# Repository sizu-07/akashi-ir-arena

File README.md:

# 明石光線

4人が1対1対1対1で遊ぶ赤外線対戦システムです。銃側はXIAO ESP32-S3 Plus、赤外線受信機3個、赤外線送信、テープLED、振動モーター、トリガー1個を使用し、Windows PCが試合を管理します。銃にブザーやリロードボタンはありません。運営はiPad、観客表示とカウントダウン音声・BGMはPCに接続したプロジェクターから操作します。現行ルールは実時間85秒・画面表示90秒×3ゲーム・1発撃破・7秒自動復活・合計キル数勝負です。詳細は [ゲーム仕様 v0.8](docs/ゲーム仕様_v0.8.md) を参照してください。

射撃・被弾・撃破・復活・試合終了の効果音は、[音声ファイルの配置方法](assets/audio/README.md)に従い `assets/audio/effects/` に入れると投影画面から再生できます。

## 現在の状態

- PC管理プログラム、iPad運営画面、投影画面、ESP32ファームウェアを収録しています。
- 来場者向け整理券受付・待機表示、整理券運営、入場QR読取、ゲーム状態連携を収録しています。
- 回路設計と銃の3Dモデルは別担当です。`hardware/circuit/` の既存KiCadデータは旧構成で、現行ゲーム版との実機確認は未完了です。
- 電気・機械設計に必要な接続条件は `specs/` にあります。
- player1〜4の個人戦用BINは `firmware/release/players-4e/` に生成済みです。4台同時の試合、連続稼働、会場での確認は未実施です。旧v0.7以前のBINは個人戦に使用できません。

## 実行方法

1. Node.js 20以上をインストールします。
2. 動作確認は `起動_デモ.cmd`、実機4台での本番運営は `起動_本番.cmd` を開きます。
3. 初回だけ必要なパッケージと設定が準備され、ゲーム運営画面が自動的に開きます。
4. ゲーム運営画面は `http://localhost:8080/`、投影画面は `http://localhost:8080/display` です。
5. 整理券の運営・来場者受付・入場QR読取は、ゲーム運営画面上部から公開サーバーの各画面を開きます。

タブレットの運営画面は、PCと同じWi-Fiに接続し、PCのWi-Fi側IPv4アドレスを使って `http://<PCのWi-Fiアドレス>:8080/` を開きます。PCの `localhost` や基板用Ethernetの `192.168.137.1` はタブレットからの接続先ではありません。PCの投影画面にある「タブレット接続QR」もWi-Fi側アドレスを表示します。IPアドレスはネットワーク接続時に変わる場合があります。

`起動_デモ.cmd` と `起動_本番.cmd` を切り替えるときは、同じポートで動いているこのシステムの旧サーバーを自動終了してから、選んだモードで起動し直します。別のアプリが8080番ポートを使っている場合は、安全のため自動終了しません。

デモ版では「デモの確認対象」で「仮想端末4台（実機なし）」と「接続した実機」を切り替えます。実機を選ぶと仮想端末を停止し、「接続済み端末だけで動作確認」で1台から開始できます。投影画面の「表示を準備」と、参加端末の接続・時刻同期・構成確認が必要です。待機中、動作確認の途中経過表示中、または終了後に切り替えられ、切り替えると戦績・残り時間を戻します。確認対象は次回のデモ起動にも引き継ぎます。実機のWi-Fi設定・端末キーは本番と共通です。デモ版は公開整理券サーバーへゲーム連携通信を行いません。

本番版には動作確認・実機モーターデモの操作を表示しません。通常ゲーム用の4台、電池状態、投影準備、開始ACKを確認して通常試合を開始します。整理券連携が設定済みなら、先に「整理券メンバーを反映」を実行してください。本番APIからの動作確認要求も拒否します。

本番では第1〜2ゲームの終了後に途中経過を15秒表示し、4台と投影画面の準備が整えば次のカウントダウンへ自動で進みます。デモでは「このゲームを終了して途中経過へ」で時間を短縮し、次ゲームを手動開始できます。両モードの「試合全体を強制終了」は残りゲームを省略します。整理券は4名全員が入場確認されるまで通常試合へ進めません。処理の分担と運営手順は [ゲーム仕様 v0.8](docs/ゲーム仕様_v0.8.md) にまとめています。

`npm run validate` はソフトウェア・4台分のBIN・実機試験記録を別々に確認します。4台同時の実機試験は未実施なので、[実機試験記録](tests/実機試験記録.csv) の v0.8 項目が完了するまで総合判定は不合格になります。

整理券の正本は公開サーバーとSupabaseに一元化しています。ローカルに別の整理券サーバーを起動しないでください。詳細は [整理券システム 運用・配置手順](docs/整理券システム.md) を参照。

~~詳しい手順は次の順で読んでください。~~

~~1. [概要と仕様](docs/01_概要と仕様.md)
2. [製作・Wi-Fi・書込み](docs/02_製作手順.md)
3. [運営と投影の操作](docs/03_操作手順.md)
4. [実機の完成確認](docs/04_完成確認チェック.md)
5. [開発者向け案内](docs/05_開発者向け.md)~~
未定のため修正中。決まり次第記入予定。

## フォルダ構成

| 場所 | 内容 |
|---|---|
| `apps/server/` | Windows PCで動く試合管理・通信サーバー |
| `apps/web/` | iPad運営画面とプロジェクター投影画面 |
| `apps/ticket-server/` | 外部整理券API、割当、認証、履歴、WebSocket |
| `apps/ticket-web/` | 来場者受付・整理券・運営・入場QR読取画面 |
| `assets/` | ルール説明動画などの共通素材 |
| `firmware/` | XIAO ESP32-S3 Plus用プログラムと書込み用BIN |
| `specs/` | GPIO、受信機3個、モーターなどのハードウェア要求 |
| `hardware/circuit/` | 回路担当者の提出先（既存KiCadデータは旧構成） |
| `hardware/gun-model/` | 銃モデル担当者の提出先 |
| `docs/` | 仕様、製作、操作、試験の説明書 |
| `tools/` | セットアップ、ビルド、書込み、検証用ツール |
| `tests/` | 自動テストと実機試験記録 |

`config/`、`data/`、`logs/`、`.local-archive/` は各PCだけで使い、GitHubには共有しません。Wi-Fiパスワード、運営PIN、銃ごとの鍵も共有しないでください。

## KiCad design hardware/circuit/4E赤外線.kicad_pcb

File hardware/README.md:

# ハードウェア担当者用

回路設計と銃の3Dモデルは別担当者が作成します。`circuit/` に残るKiCadデータは旧構成です。

- 回路・PCBデータの提出先：`circuit/`
- 銃の3Dモデル・STL・組立図の提出先：`gun-model/`
- 共通の要求条件：`../specs/hardware-profile.json`
- 部品候補と変更点：`../specs/component-plan.csv`
- ゲーム・操作・表示条件：`../docs/ゲーム仕様_v0.7.md`
- 検査条件：`../tests/実機試験記録.csv`

現在の `circuit/` のKiCadデータは旧構成を含み、v0.7の実装確認済み回路ではありません。新設計では銃の操作入力をトリガー1個にし、リロード・モード用スイッチとブザーを設けず、6個のLEDと振動モーターを接続してください。銃IDとWi-FiはUSBで登録するため、組立後もUSB端子にアクセスできる筐体が必要です。電源の投入・遮断方法は回路・筐体担当者が確定してください。

担当者は採用部品、端子割当、電源定格、基板寸法、取付位置が確定した時点で、このREADMEも更新してください。特に射撃時の短い振動と赤外線送信が同時に動作する際の電圧降下を実測してください。

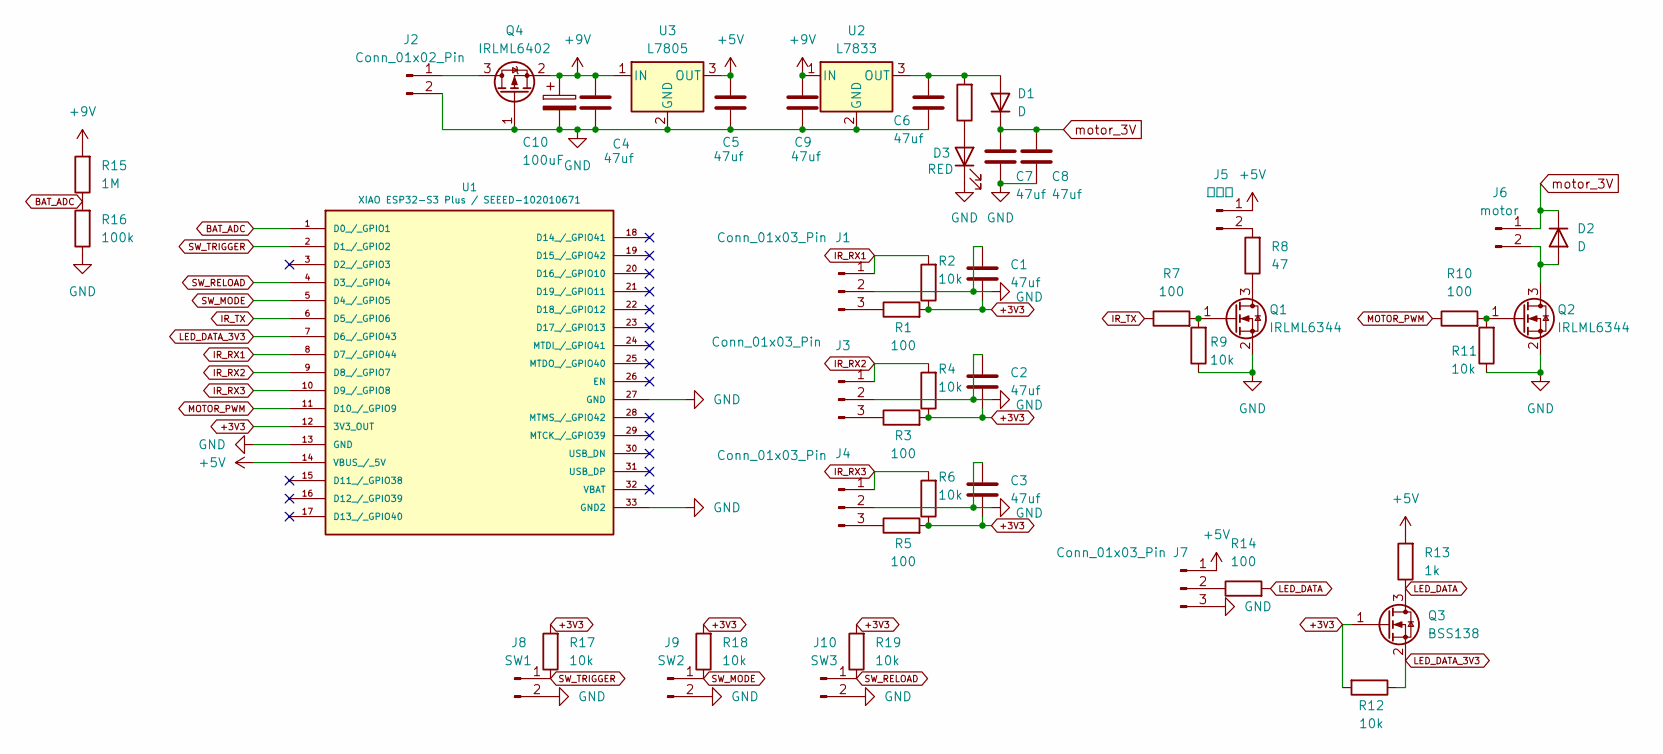
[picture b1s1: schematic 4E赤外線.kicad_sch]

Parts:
C1, C2, C3, C4, C5, C6, C9: 47uf; C_0603_1608Metric
C7, C8: 47uf; C_0805_2012Metric
C10: 100uF; CP_Elec_8x6.5
D1, D2: D; D_MicroSMP_AK
D3: RED; LED_0603_1608Metric
J1, J3, J4, J7: Conn_01x03_Pin; JST_XH_B3B-XH-A_1x03_P2.50mm_Vertical
J2: Conn_01x02_Pin; JST_XH_B2B-XH-A_1x02_P2.50mm_Vertical
J5: 赤外線; JST_XH_B2B-XH-A_1x02_P2.50mm_Vertical
J6: motor; JST_XH_B2B-XH-A_1x02_P2.50mm_Vertical
J8: SW1; JST_XH_B2B-XH-A_1x02_P2.50mm_Vertical
J9: SW2; JST_XH_B2B-XH-A_1x02_P2.50mm_Vertical
J10: SW3; JST_XH_B2B-XH-A_1x02_P2.50mm_Vertical
Q1, Q2: IRLML6344; SOT-23
Q3: BSS138; SOT-23
Q4: IRLML6402; SOT-23
R1, R3, R5, R7, R10, R14: 100; R_0603_1608Metric
R2, R4, R6, R9, R11, R12, R17, R18, R19: 10k; R_0603_1608Metric
R8: 47; R_0603_1608Metric
R13: 1k; R_0603_1608Metric
R15: 1M; R_0805_2012Metric
R16: 100k; R_0805_2012Metric
R20: 1k; R_0603_1608Metric; LCSC C23345
U1: XIAO ESP32-S3 Plus / SEEED-102010671; XIAO-ESP32-S3-Plus-SMD; MPN SEEED-102010671
U2: L7833; TO-252-3-L1_NMD
U3: L7805; TO-252-3-L1_NMD

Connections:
+3V3: C1.2, C2.2, C3.2, Q3.1 (G), R1.2, R2.1, R3.2, R4.1, R5.2, R6.1, R12.2, R17.2, R18.2, R19.2, U1.12 (3V3_OUT)
+5V: C5.1, J5.1, J7.1, R13.2, U1.14 (VBUS_/_5V), U3.3 (OUT)
+9V: C4.1, C9.1, C10.1, Q4.2 (S), R15.2, U2.1 (IN), U3.1 (IN)
BAT_ADC: R15.1, R16.2, U1.1 (D0_/_GPIO1)
GND: C1.1, C2.1, C3.1, C4.2, C5.2, C6.2, C7.2, C8.2, C9.2, C10.2, D3.1 (K), J1.2, J2.2, J3.2, J4.2, J7.3, J8.2, J9.2, J10.2, Q1.2 (S), Q2.2 (S), Q4.1 (G), R9.1, R11.1, R16.1, U1.13 (GND), U1.27 (GND), U1.33 (GND2), U2.2 (GND), U3.2 (GND)
IR_RX1: J1.1, R2.2, U1.8 (D7_/_GPIO44)
IR_RX2: J3.1, R4.2, U1.9 (D8_/_GPIO7)
IR_RX3: J4.1, R6.2, U1.10 (D9_/_GPIO8)
IR_TX: R7.1, U1.6 (D5_/_GPIO6)
LED_DATA: Q3.3 (D), R13.1, R14.2
LED_DATA_3V3: Q3.2 (S), R12.1, U1.7 (D6_/_GPIO43)
MOTOR_PWM: R10.1, U1.11 (D10_/_GPIO9)
unnamed: C6.1, D1.2 (A), R20.2, U2.3 (OUT)
unnamed: D2.2 (A), J6.2, Q2.3 (D)
unnamed: D3.2 (A), R20.1
unnamed: J1.3, R1.1
unnamed: J2.1, Q4.3 (D)
unnamed: J3.3, R3.1
unnamed: J4.3, R5.1
unnamed: J5.2, R8.2
unnamed: J7.2, R14.1
unnamed: Q1.3 (D), R8.1
unnamed: Q1.1 (G), R7.2, R9.2
unnamed: Q2.1 (G), R10.2, R11.2
SW_MODE: J9.1, R18.1, U1.5 (D4_/_GPIO5)
SW_RELOAD: J10.1, R19.1, U1.4 (D3_/_GPIO4)
SW_TRIGGER: J8.1, R17.1, U1.2 (D1_/_GPIO2)
motor_3V: C7.1, C8.1, D1.1 (K), D2.1 (K), J6.1

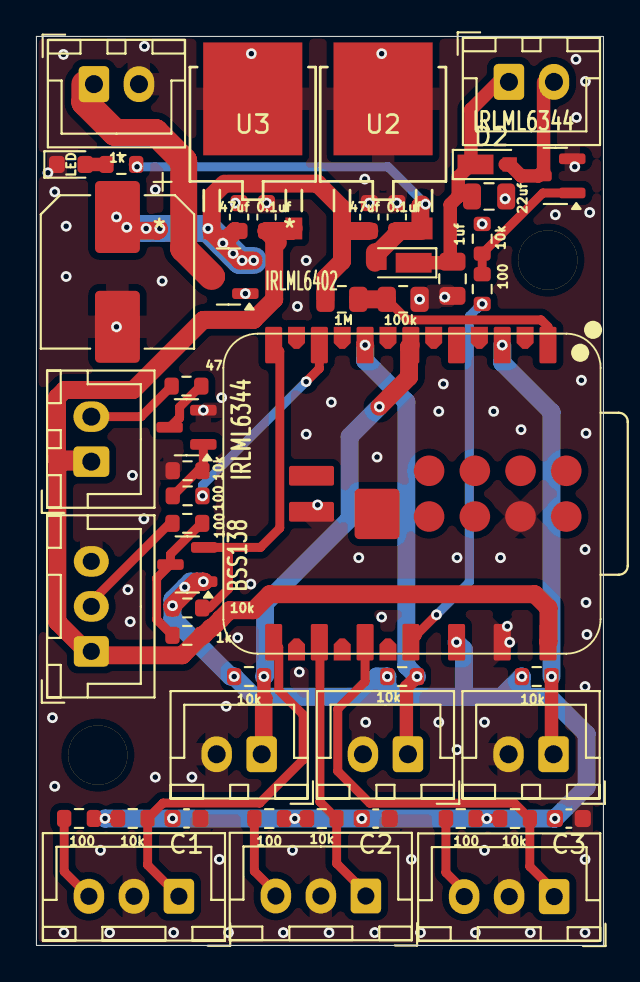
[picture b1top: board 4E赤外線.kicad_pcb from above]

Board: 2 copper layers, 31.5 x 50.5 mm, 50 parts (0 on the bottom side), 28 nets.

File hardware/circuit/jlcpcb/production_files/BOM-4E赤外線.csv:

Comment,Designator,Footprint,LCSC,Quantity
1k,R20,R_0603_1608Metric,C23345,1
47uf,"C1,C2,C3,C4,C5,C6,C9",C_0603_1608Metric,C140782,7
IRLML6344,Q1,SOT-23,,1
10k,R9,R_0603_1608Metric,,1
47,R8,R_0603_1608Metric,,1
100,R7,R_0603_1608Metric,,1
Conn_01x03_Pin,J7,JST_XH_B3B-XH-A_1x03_P2.50mm_Vertical,,1
10k,R11,R_0603_1608Metric,,1
D,D2,D_MicroSMP_AK,,1
C_Polarized,C10,CP_Elec_8x6.5,,1
47uf,C7,C_0805_2012Metric,,1
Conn_01x02_Pin,J2,JST_XH_B2B-XH-A_1x02_P2.50mm_Vertical,,1
IRLML6402,Q4,SOT-23,,1
LED,D3,LED_0603_1608Metric,,1
D,D1,D_MicroSMP_AK,,1
1M,R15,R_0805_2012Metric,,1
motor,J6,JST_XH_B2B-XH-A_1x02_P2.50mm_Vertical,,1
L7805,U3,TO-252-3-L1_NMD,,1
100k,R16,R_0805_2012Metric,,1
IRLML6344,Q2,SOT-23,,1
100,R10,R_0603_1608Metric,,1
47uf,C8,C_0805_2012Metric,,1
L7833,U2,TO-252-3-L1_NMD,,1
赤外線,J5,JST_XH_B2B-XH-A_1x02_P2.50mm_Vertical,,1
XIAO ESP32-S3 Plus / SEEED-102010671,U1,XIAO-ESP32-S3-Plus-SMD,,1
10k,R12,R_0603_1608Metric,,1
100,R3,R_0603_1608Metric,,1
Conn_01x03_Pin,J3,JST_XH_B3B-XH-A_1x03_P2.50mm_Vertical,,1
Conn_01x03_Pin,J4,JST_XH_B3B-XH-A_1x03_P2.50mm_Vertical,,1
10k,R4,R_0603_1608Metric,,1
Conn_01x03_Pin,J1,JST_XH_B3B-XH-A_1x03_P2.50mm_Vertical,,1
10k,R6,R_0603_1608Metric,,1
100,R14,R_0603_1608Metric,,1
BSS138,Q3,SOT-23,,1
SW2,J9,JST_XH_B2B-XH-A_1x02_P2.50mm_Vertical,,1
1k,R13,R_0603_1608Metric,,1
10k,R19,R_0603_1608Metric,,1
10k,R17,R_0603_1608Metric,,1
100,R5,R_0603_1608Metric,,1
SW3,J10,JST_XH_B2B-XH-A_1x02_P2.50mm_Vertical,,1
100,R1,R_0603_1608Metric,,1
SW1,J8,JST_XH_B2B-XH-A_1x02_P2.50mm_Vertical,,1
10k,R2,R_0603_1608Metric,,1
10k,R18,R_0603_1608Metric,,1

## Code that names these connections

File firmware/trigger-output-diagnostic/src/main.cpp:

#include <Arduino.h>
#include <driver/rmt.h>

#if !CONFIG_IDF_TARGET_ESP32S3
#error "Trigger output diagnostic requires XIAO ESP32-S3 Plus"
#endif

// Legacy 4E赤外線 PCB. These pins differ from the current v0.7 profile.
constexpr uint8_t SW1_PIN = 2;       // J8 / SW_TRIGGER, closed to GND
constexpr uint8_t SW2_PIN = 5;       // J9 / SW_MODE
constexpr uint8_t SW3_PIN = 4;       // J10 / SW_RELOAD
constexpr uint8_t MOTOR_PIN = 9;     // MOTOR_PWM -> Q2 gate
constexpr uint8_t IR_PIN = 6;        // IR_TX -> Q1 gate
constexpr uint8_t LED_PIN = 43;      // LED_DATA_3V3 -> level shifter -> J7
constexpr uint8_t LED_COUNT = 8;
constexpr uint8_t WHITE_20_PERCENT = 51;  // 20% of 255 per RGB channel
constexpr uint32_t DEBOUNCE_MS = 20;
constexpr uint32_t REPORT_INTERVAL_MS = 500;
constexpr uint8_t IR_PWM_CHANNEL = 0;
constexpr uint32_t IR_CARRIER_HZ = 38000;
constexpr uint8_t IR_DUTY_33_PERCENT = 85;  // 85 / 255
constexpr rmt_channel_t LED_RMT_CHANNEL = RMT_CHANNEL_1;
// RMT clock: 80 MHz APB / 2 = 40 MHz, one tick = 25 ns.
// WS2812B ECO: each bit is 1.25 us; low between frames exceeds 280 us.
constexpr uint16_t LED_0_HIGH_TICKS = 13;  // 0.325 us
constexpr uint16_t LED_0_LOW_TICKS = 37;   // 0.925 us
constexpr uint16_t LED_1_HIGH_TICKS = 26;  // 0.650 us
constexpr uint16_t LED_1_LOW_TICKS = 24;   // 0.600 us
constexpr uint16_t LED_RESET_US = 300;
static_assert(LED_0_HIGH_TICKS + LED_0_LOW_TICKS == 50, "WS2812B zero bit timing");
static_assert(LED_1_HIGH_TICKS + LED_1_LOW_TICKS == 50, "WS2812B one bit timing");

int rawSw1 = HIGH;
int stableSw1 = HIGH;
uint32_t rawChangedAt = 0;
uint32_t lastReportAt = 0;
bool armed = false;
bool outputsOn = false;
bool ledReady = false;

const char* levelName(int level) { return level == LOW ? "LOW" : "HIGH"; }
const char* stateName(int level) { return level == LOW ? "PRESSED" : "RELEASED"; }

bool writeLeds(bool on) {
  if (!ledReady) return false;
  rmt_item32_t items[LED_COUNT * 24]{};
  size_t count = 0;
  const uint8_t value = on ? WHITE_20_PERCENT : 0;
  // WS2812 uses GRB order. White has the same value on all channels.
  for (uint8_t pixel = 0; pixel < LED_COUNT; ++pixel) {
    for (uint8_t channel = 0; channel < 3; ++channel) {
      for (int bit = 7; bit >= 0; --bit) {
        const bool one = value & (1u << bit);
        auto& item = items[count++];
        item.level0 = 1;
        item.duration0 = one ? LED_1_HIGH_TICKS : LED_0_HIGH_TICKS;
        item.level1 = 0;
        item.duration1 = one ? LED_1_LOW_TICKS : LED_0_LOW_TICKS;
      }
    }
  }
  const esp_err_t result = rmt_write_items(LED_RMT_CHANNEL, items, count, true);
  delayMicroseconds(LED_RESET_US);  // Low-level reset/latch interval
  if (result != ESP_OK) Serial.printf("ERROR LED RMT code=%d\n", result);
  return result == ESP_OK;
}

void stopOutputs() {
  digitalWrite(MOTOR_PIN, LOW);
  ledcWrite(IR_PWM_CHANNEL, 0);
  writeLeds(false);
  outputsOn = false;
}

void startOutputs() {
  if (!writeLeds(true)) {
    stopOutputs();
    Serial.println("ERROR OUTPUT START: LED transfer failed");
    return;
  }
  ledcWrite(IR_PWM_CHANNEL, IR_DUTY_33_PERCENT);
  digitalWrite(MOTOR_PIN, HIGH);
  outputsOn = true;
}

void reportState(const char* kind) {
  Serial.printf("%s time_ms=%lu SW1/J8/GPIO2=%s(%s) SW2/J9/GPIO5=%s(%s) SW3/J10/GPIO4=%s(%s) motor=%s led8_white20=%s ir38k=%s armed=%s\n",
                kind, static_cast<unsigned long>(millis()),
                levelName(digitalRead(SW1_PIN)), stateName(digitalRead(SW1_PIN)),
                levelName(digitalRead(SW2_PIN)), stateName(digitalRead(SW2_PIN)),
                levelName(digitalRead(SW3_PIN)), stateName(digitalRead(SW3_PIN)),
                outputsOn ? "ON" : "OFF", outputsOn ? "ON" : "OFF",
                outputsOn ? "ON" : "OFF", armed ? "YES" : "NO");
}

void setup() {
  // Keep the MOSFET gates inactive before configuring any peripherals.
  digitalWrite(MOTOR_PIN, LOW);
  pinMode(MOTOR_PIN, OUTPUT);
  digitalWrite(IR_PIN, LOW);
  pinMode(IR_PIN, OUTPUT);
  digitalWrite(LED_PIN, LOW);
  pinMode(LED_PIN, OUTPUT);
  pinMode(SW1_PIN, INPUT_PULLUP);
  pinMode(SW2_PIN, INPUT_PULLUP);
  pinMode(SW3_PIN, INPUT_PULLUP);
  Serial.begin(115200);

  ledcSetup(IR_PWM_CHANNEL, IR_CARRIER_HZ, 8);
  ledcAttachPin(IR_PIN, IR_PWM_CHANNEL);
  ledcWrite(IR_PWM_CHANNEL, 0);

  rmt_config_t led = RMT_DEFAULT_CONFIG_TX(static_cast<gpio_num_t>(LED_PIN), LED_RMT_CHANNEL);
  led.clk_div = 2;  // 25 ns RMT tick; WS2812B ECO uses 1.25 us per bit.
  led.tx_config.idle_output_en = true;
  led.tx_config.idle_level = RMT_IDLE_LEVEL_LOW;
  const esp_err_t configResult = rmt_config(&led);
  const esp_err_t installResult = configResult == ESP_OK
                                      ? rmt_driver_install(LED_RMT_CHANNEL, 0, 0)
                                      : configResult;
  ledReady = installResult == ESP_OK;
  if (!ledReady) Serial.printf("ERROR LED INIT code=%d; outputs disabled\n", installResult);
  else writeLeds(false);

  rawSw1 = stableSw1 = digitalRead(SW1_PIN);
  rawChangedAt = millis();
  // Require a new HIGH -> LOW transition, including after a reboot with SW1 held.
  armed = stableSw1 == HIGH;
  Serial.println("TRIGGER OUTPUT DIAGNOSTIC READY; SW1 LOW=pressed, debounce=20ms");
  Serial.println("SW1 held: motor ON, 8 LEDs white 20%, IR carrier 38kHz ON; released: all OFF");
  reportState("START");
  lastReportAt = millis();
}

void loop() {
  const uint32_t now = millis();
  const int current = digitalRead(SW1_PIN);
  if (current != rawSw1) {
    rawSw1 = current;
    rawChangedAt = now;
  }
  if (current != stableSw1 && now - rawChangedAt >= DEBOUNCE_MS) {
    stableSw1 = current;
    Serial.printf("EDGE time_ms=%lu SW1/J8/GPIO2=%s(%s)\n",
                  static_cast<unsigned long>(now), levelName(current), stateName(current));
    if (current == HIGH) {
      stopOutputs();
      armed = true;
      Serial.println("EVENT OUTPUTS OFF");
    } else if (armed && ledReady) {
      armed = false;
      startOutputs();
      if (outputsOn) Serial.println("EVENT OUTPUTS ON motor=ON led8_white20=ON ir38k=ON");
    }
  }
  if (now - lastReportAt >= REPORT_INTERVAL_MS) {
    lastReportAt = now;
    reportState("STATE");
  }
  delay(1);
}
